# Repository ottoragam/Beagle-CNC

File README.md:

# Beagle-CNC
4 Axis Open Source Beaglebone Cape based on the BeBoPr++

----------------------------------------------------------------------
Beagle-CNC (c) by Gino Magarotto

Beagle-CNC is licensed under a
Creative Commons Attribution-ShareAlike 3.0 Unported License.

You should have received a copy of the license along with this
work.  If not, see <http://creativecommons.org/licenses/by-sa/3.0/>.

----------------------------------------------------------------------

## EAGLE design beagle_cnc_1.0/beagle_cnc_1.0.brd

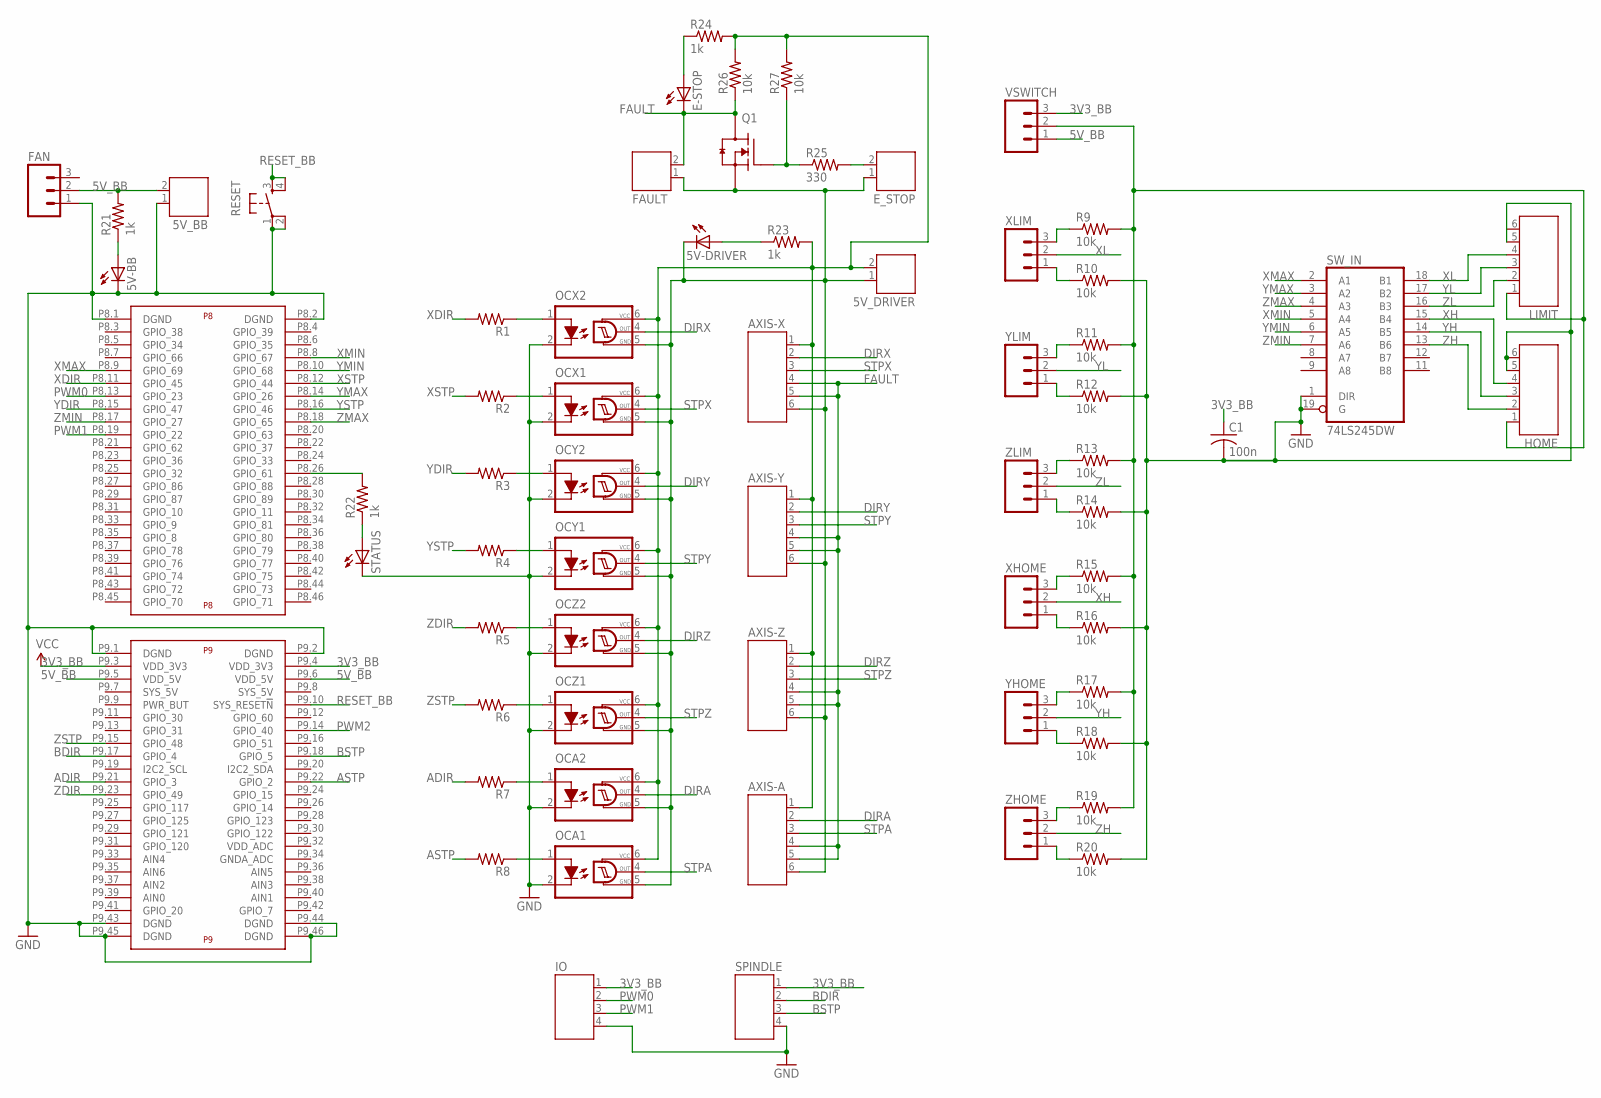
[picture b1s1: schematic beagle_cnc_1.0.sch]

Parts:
5V-BB, 5V-DRIVER: LEDCHIP-LED0603; CHIP-LED0603
5V_BB, 5V_DRIVER: JST-PH2
AXIS-A: JST-PH6
AXIS-X: JST-PH6
AXIS-Y: JST-PH6
AXIS-Z: JST-PH6
C1: 100n; C0603
E-STOP: LEDCHIP-LED0603; CHIP-LED0603
E_STOP: JST-PH2
FAN: M03POLAR; MOLEX-1X3
FAULT: JST-PH2
HOME: JST-PH6
IO: JST-PH4
LIMIT: JST-PH6
OCA1, OCA2: H11L1MS; DIL6-SMD
OCX1, OCX2: H11L1MS; DIL6-SMD
OCY1, OCY2: H11L1MS; DIL6-SMD
OCZ1, OCZ2: H11L1MS; DIL6-SMD
Q1: MOSFET-NCH_SOT-23; SOT95P280X135-3N
R1, R2, R3, R4, R5, R6, R7, R8: R-US_R0603; R0603
R9, R10, R11, R12, R13, R14, R15, R16, R17, R18, R19, R20, R26, R27: 10k; R0603
R21, R22, R23, R24: 1k; R0603
R25: 330; R0603
RESET: TAC_SWITCHSMD; TACTILE-SWITCH-SMD
SPINDLE: JST-PH4
STATUS: LEDCHIP-LED0603; CHIP-LED0603
SW_IN: 74LS245DW; SO20W
U$1: BEAGLE_BONE_BLACK_CAPE
VSWITCH: M03PTH; 1X03
XHOME: M03PTH; 1X03
XLIM: M03PTH; 1X03
YHOME: M03PTH; 1X03
YLIM: M03PTH; 1X03
ZHOME: M03PTH; 1X03
ZLIM: M03PTH; 1X03

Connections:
3V3_BB: C1.1, IO.1, SPINDLE.1, SW_IN.20 (VCC), U$1.P9.3 (VDD_3V3), U$1.P9.4 (VDD_3V3), VSWITCH.3
5V_BB: 5V_BB.2, FAN.2, R21.2, U$1.P9.5 (VDD_5V), U$1.P9.6 (VDD_5V), VSWITCH.1
ADIR: R7.2, U$1.P9.21 (GPIO_3)
ASTP: R8.2, U$1.P9.22 (GPIO_2)
AXISGND: 5V-DRIVER.C, 5V_DRIVER.1, AXIS-A.6, AXIS-X.6, AXIS-Y.6, AXIS-Z.6, E_STOP.1, FAULT.1, OCA1.5 (GND), OCA2.5 (GND), OCX1.5 (GND), OCX2.5 (GND), OCY1.5 (GND), OCY2.5 (GND), OCZ1.5 (GND), OCZ2.5 (GND), Q1.2 (S)
BDIR: SPINDLE.2, U$1.P9.17 (GPIO_4)
BLABLA: HOME.1, LIMIT.1, R9.2, R11.2, R13.2, R15.2, R17.2, R19.2, VSWITCH.2
BSTP: SPINDLE.3, U$1.P9.18 (GPIO_5)
DIRA: AXIS-A.2, OCA2.4 (OUT)
DIRX: AXIS-X.2, OCX2.4 (OUT)
DIRY: AXIS-Y.2, OCY2.4 (OUT)
DIRZ: AXIS-Z.2, OCZ2.4 (OUT)
FAULT: AXIS-A.4, AXIS-A.5, AXIS-X.4, AXIS-X.5, AXIS-Y.4, AXIS-Y.5, AXIS-Z.4, AXIS-Z.5, E-STOP.C, FAULT.2, Q1.3 (D), R26.1
GND: 5V-BB.C, 5V_BB.1, C1.2, FAN.1, HOME.5, HOME.6, IO.4, LIMIT.5, LIMIT.6, OCA1.2 (C), OCA2.2 (C), OCX1.2 (C), OCX2.2 (C), OCY1.2 (C), OCY2.2 (C), OCZ1.2 (C), OCZ2.2 (C), R10.2, R12.2, R14.2, R16.2, R18.2, R20.2, RESET.1, RESET.2, SPINDLE.4, STATUS.C, SW_IN.1 (DIR), SW_IN.10 (GND), SW_IN.19 (G), U$1.P8.1 (DGND), U$1.P8.2 (DGND), U$1.P9.1 (DGND), U$1.P9.2 (DGND), U$1.P9.43 (DGND), U$1.P9.44 (DGND), U$1.P9.45 (DGND), U$1.P9.46 (DGND)
unnamed: 5V-BB.A, R21.1
unnamed: OCA1.1 (A), R8.1
unnamed: 5V-DRIVER.A, R23.1
unnamed: R22.1, STATUS.A
unnamed: OCA2.1 (A), R7.1
unnamed: OCZ1.1 (A), R6.1
unnamed: R9.1, XLIM.3
unnamed: OCZ2.1 (A), R5.1
unnamed: E-STOP.A, R24.1
unnamed: OCY1.1 (A), R4.1
unnamed: OCY2.1 (A), R3.1
unnamed: OCX1.1 (A), R2.1
unnamed: OCX2.1 (A), R1.1
unnamed: R10.1, XLIM.1
unnamed: R11.1, YLIM.3
unnamed: R12.1, YLIM.1
unnamed: R13.1, ZLIM.3
unnamed: R14.1, ZLIM.1
unnamed: R15.1, XHOME.3
unnamed: R16.1, XHOME.1
unnamed: R17.1, YHOME.3
unnamed: R18.1, YHOME.1
unnamed: R19.1, ZHOME.3
unnamed: R20.1, ZHOME.1
unnamed: Q1.1 (G), R25.1, R27.1
unnamed: E_STOP.2, R25.2
unnamed: 5V_DRIVER.2, AXIS-A.1, AXIS-X.1, AXIS-Y.1, AXIS-Z.1, OCA1.6 (VCC), OCA2.6 (VCC), OCX1.6 (VCC), OCX2.6 (VCC), OCY1.6 (VCC), OCY2.6 (VCC), OCZ1.6 (VCC), OCZ2.6 (VCC), R23.2, R24.2, R26.2, R27.2
PWM0: IO.2, U$1.P8.13 (GPIO_23)
PWM1: IO.3, U$1.P8.19 (GPIO_22)
PWM2: U$1.P9.14 (GPIO_40)
RESET_BB: RESET.3, RESET.4, U$1.P9.10 (SYS_RESET!N)
STATUS: R22.2, U$1.P8.26 (GPIO_61)
STPA: AXIS-A.3, OCA1.4 (OUT)
STPX: AXIS-X.3, OCX1.4 (OUT)
STPY: AXIS-Y.3, OCY1.4 (OUT)
STPZ: AXIS-Z.3, OCZ1.4 (OUT)
XDIR: R1.2, U$1.P8.11 (GPIO_45)
XH: HOME.4, SW_IN.15 (B4), XHOME.2
XL: LIMIT.4, SW_IN.18 (B1), XLIM.2
XMAX: SW_IN.2 (A1), U$1.P8.9 (GPIO_69)
XMIN: SW_IN.5 (A4), U$1.P8.8 (GPIO_67)
XSTP: R2.2, U$1.P8.12 (GPIO_44)
YDIR: R3.2, U$1.P8.15 (GPIO_47)
YH: HOME.3, SW_IN.14 (B5), YHOME.2
YL: LIMIT.3, SW_IN.17 (B2), YLIM.2
YMAX: SW_IN.3 (A2), U$1.P8.14 (GPIO_26)
YMIN: SW_IN.6 (A5), U$1.P8.10 (GPIO_68)
YSTP: R4.2, U$1.P8.16 (GPIO_46)
ZDIR: R5.2, U$1.P9.23 (GPIO_49)
ZH: HOME.2, SW_IN.13 (B6), ZHOME.2
ZL: LIMIT.2, SW_IN.16 (B3), ZLIM.2
ZMAX: SW_IN.4 (A3), U$1.P8.18 (GPIO_65)
ZMIN: SW_IN.7 (A6), U$1.P8.17 (GPIO_27)
ZSTP: R6.2, U$1.P9.15 (GPIO_48)

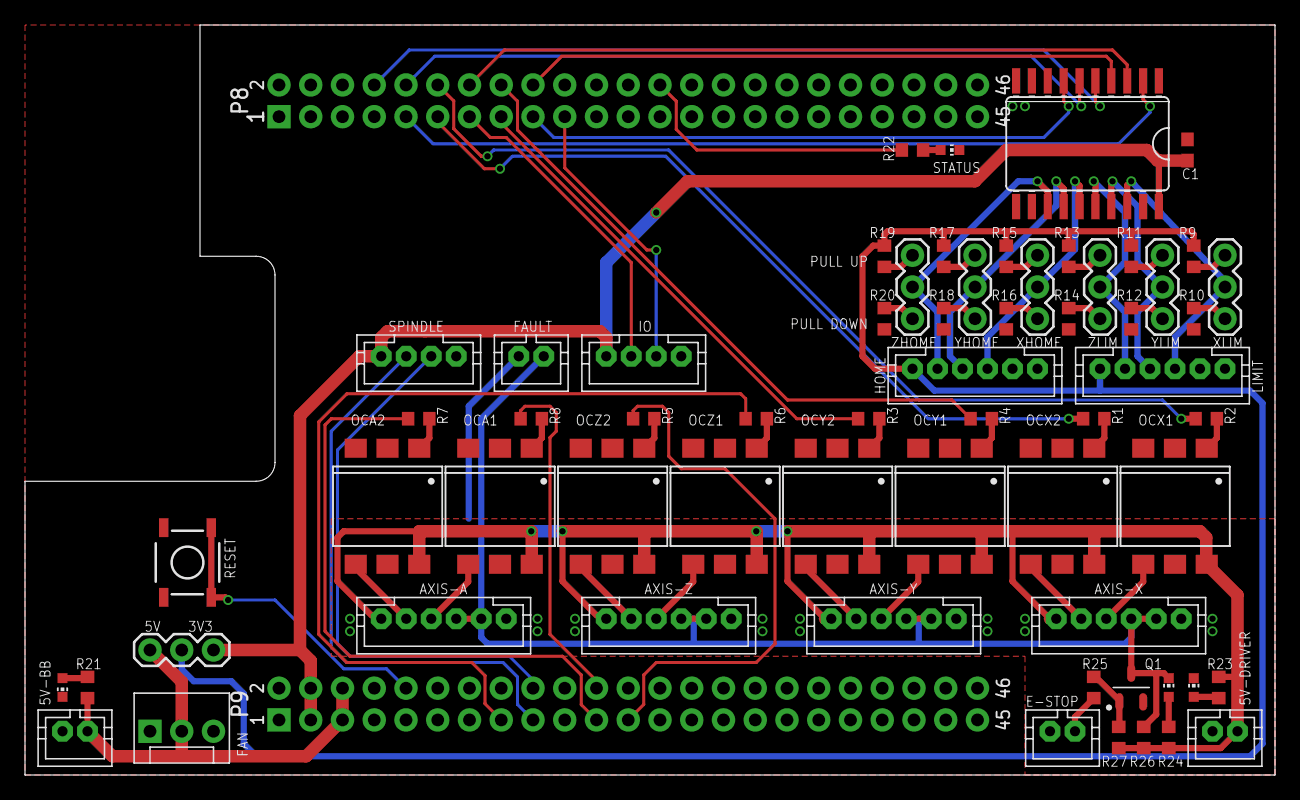
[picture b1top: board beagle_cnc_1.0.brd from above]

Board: 2 copper layers, 100.0 x 60.0 mm, 64 parts (0 on the bottom side), 67 nets.

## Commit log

2017-01-29 :confetti_ball: Added .gitattributes & .gitignore files
2017-01-29 4 axis machine controller
2017-01-29 add files

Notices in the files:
parts and their libraries:
SparkFun-Connectors: Licensing: Creative Commons ShareAlike 4.0 International - https://creativecommons.org/licenses/by-sa/4.0
